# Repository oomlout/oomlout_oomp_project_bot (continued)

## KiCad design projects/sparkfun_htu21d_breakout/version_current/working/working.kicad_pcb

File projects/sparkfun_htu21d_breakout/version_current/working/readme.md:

# OOMP Project  
## HTU21D_Breakout  by sparkfun  
  
oomp key: oomp_projects_flat_sparkfun_htu21d_breakout  
(snippet of original readme)  
  
**NOTE:** *This product has been retired from our catalog. If you are looking for more up-to-date info, please check out some of these resources to see how other users are still hacking and improving on this product.*  
* *[SparkFun Forum](https://forum.sparkfun.com/)*  
* *[Comments Here on GitHub](https://github.com/sparkfun/HTU21D_Breakout/issues)*  
  
*We recommend looking at the [Si7021](https://www.sparkfun.com/products/13763), which is a drop-in replacement for the HTU21D. It uses the same address and methods to read the sensor.*  
  
SparkFun Humidity and Temperature Sensor Breakout - HTU21D  
===========================================================  

[*SparkFun Humidity and Temperature Sensor Breakout - HTU21D (SEN-12064)*](https://www.sparkfun.com/products/12064)  
  
This is a breadboard friendly breakout board for the Measurement Specialties high-precision, low-power digital humidity sensor.  
  
Repository Contents  
-------------------  
* **/Firmware** - Example code   
* **/Hardware** - Eagle design files (.brd, .sch)  
* **/Libraries** - Libraries for use with the <PRODUCT NAME>  
* **/Production** - Production panel files (.brd)  
  
Documentation  
--------------  
* **[Library](https://github.com/sparkfun/SparkFun_HTU21D_Breakout_Arduino_Library)** - Arduino library for the HTU21D.  
* **[Hookup Guide](https://learn.sparkfun.com/tutorials/htu21d-humidity-  
  full source readme at [readme_src.md](readme_src.md)  
  
source repo at: [https://github.com/sparkfun/HTU21D_Breakout](https://github.com/sparkfun/HTU21D_Breakout)  
## Board  

## Schematic  

[schematic pdf](working_schematic.pdf)  
## Images

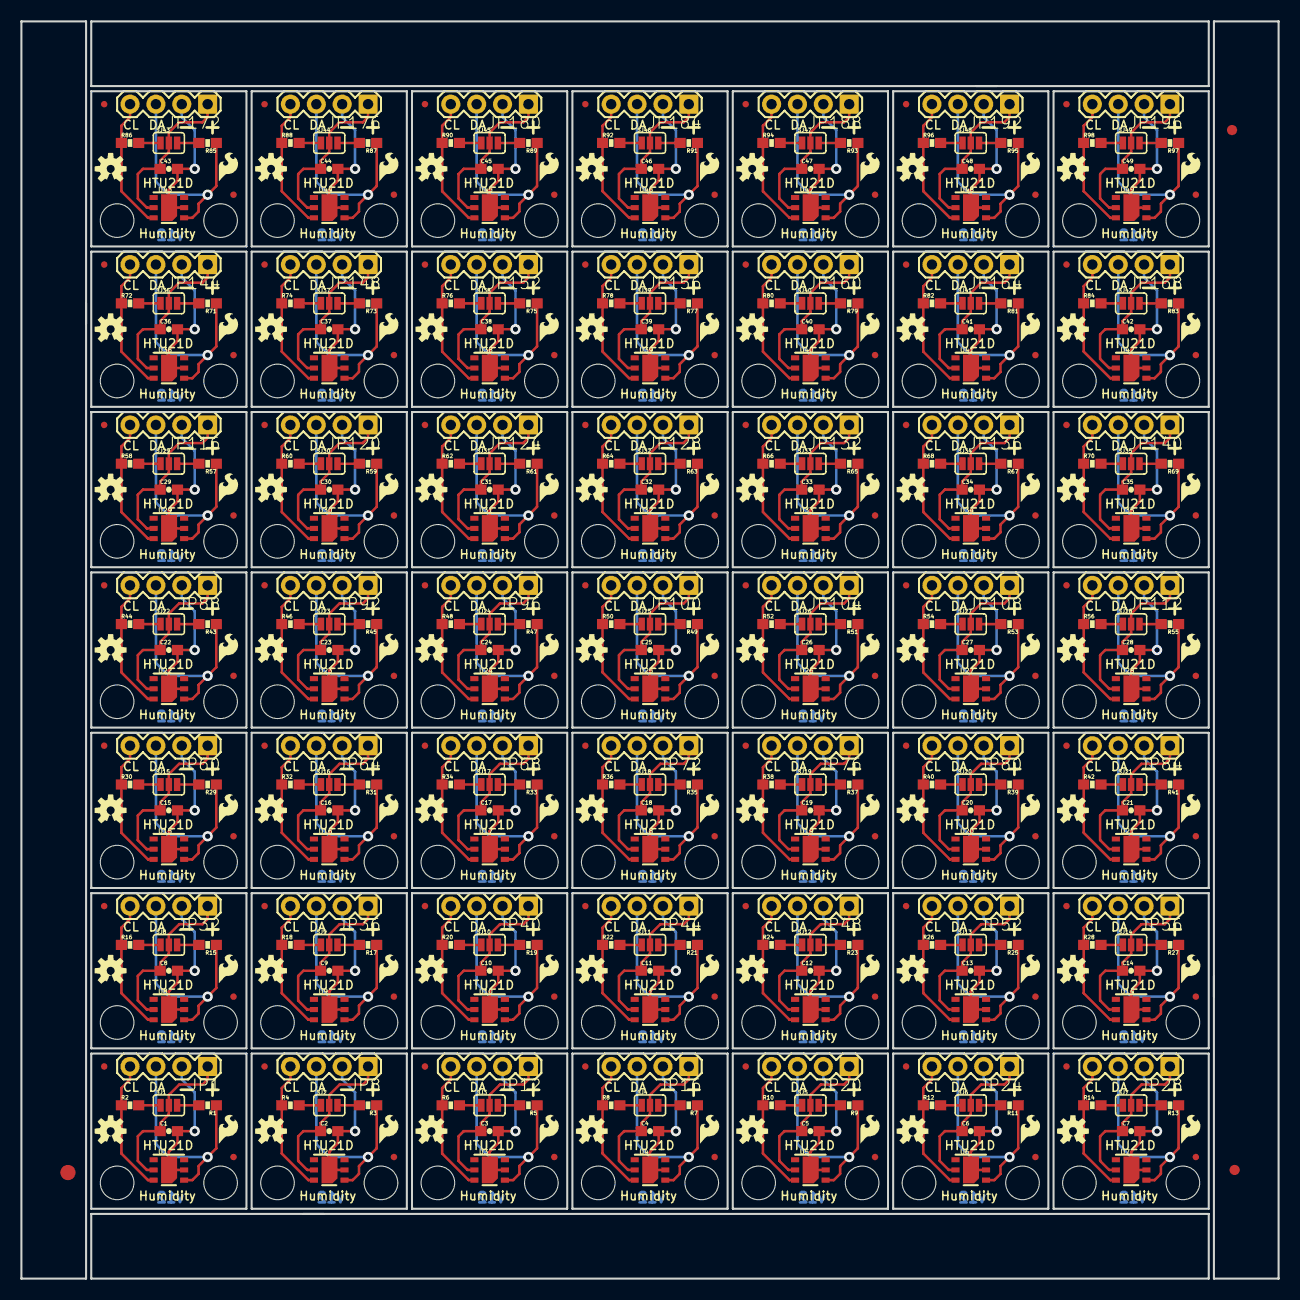
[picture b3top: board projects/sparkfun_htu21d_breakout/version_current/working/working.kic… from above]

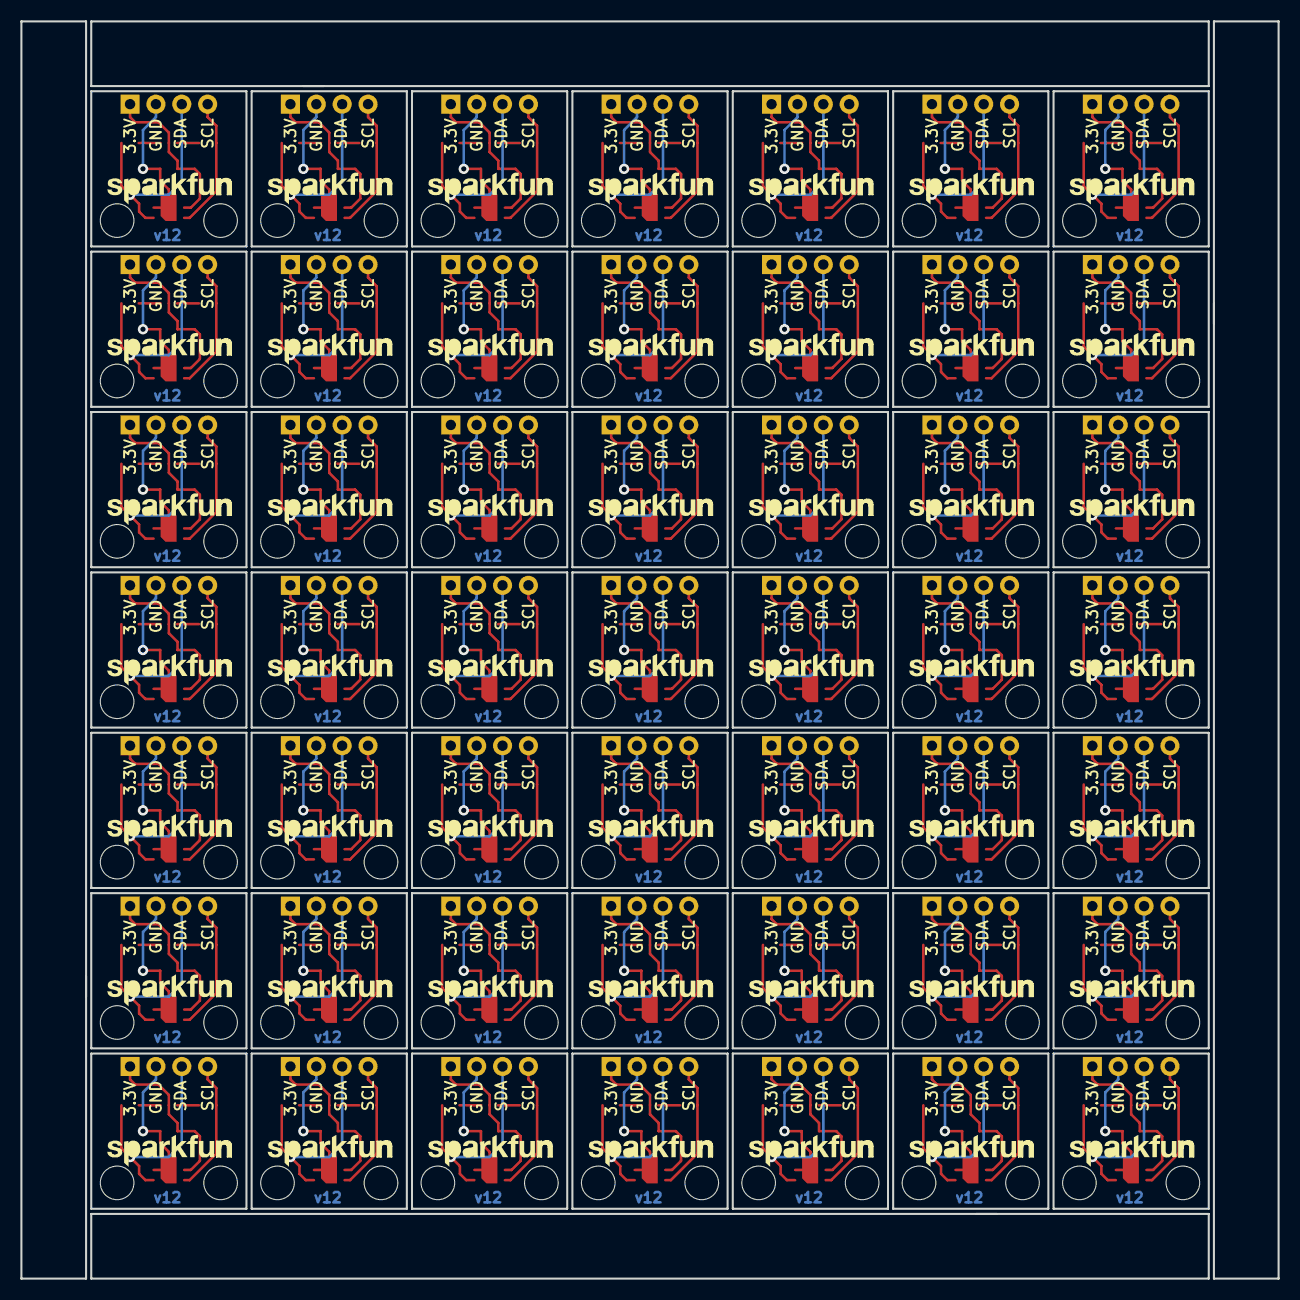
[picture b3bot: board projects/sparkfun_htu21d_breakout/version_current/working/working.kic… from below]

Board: 2 copper layers, 123.4 x 123.4 mm, 640 parts (49 on the bottom side), 294 nets.

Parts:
C1, C2, C3, C4, C5, C6, C7, C8, C9, C10, C11, C12, C13, C14, C15, C16, C17, C18, C19, C20, C21, C22, C23, C24, C25, C26, C27, C28, C29, C30, C31, C32, C33, C34, C35, C36, C37, C38, C39, C40, C41, C42, C43, C44, C45, C46, C47, C48, C49: 0.1uF; 0603-CAP
E$1: FIDUCIAL-1.5X3
E$4, E$5: FIDUCIAL-1X2
JP1, JP8, JP12, JP16, JP20, JP24, JP28, JP32, JP36, JP40, JP44, JP48, JP52, JP56, JP60, JP64, JP68, JP72, JP76, JP80, JP84, JP88, JP92, JP96, JP100, JP104, JP108, JP112, JP116, JP120, JP124, JP128, JP132, JP136, JP140, JP144, JP148, JP152, JP156, JP160, JP164, JP168, JP172, JP176, JP180, JP184, JP188, JP192, JP196: 1X04
JP2, JP5, JP9, JP13, JP17, JP21, JP25, JP29, JP33, JP37, JP41, JP45, JP49, JP53, JP57, JP61, JP65, JP69, JP73, JP77, JP81, JP85, JP89, JP93, JP97, JP101, JP105, JP109, JP113, JP117, JP121, JP125, JP129, JP133, JP137, JP141, JP145, JP149, JP153, JP157, JP161, JP165, JP169, JP173, JP177, JP181, JP185, JP189, JP193: LOGO-SFENW2; SFE-NEW-WEB
JP3, JP4, JP6, JP7, JP10, JP11, JP14, JP15, JP18, JP19, JP22, JP23, JP26, JP27, JP30, JP31, JP34, JP35, JP38, JP39, JP42, JP43, JP46, JP47, JP50, JP51, JP54, JP55, JP58, JP59, JP62, JP63, JP66, JP67, JP70, JP71, JP74, JP75, JP78, JP79, JP82, JP83, JP86, JP87, JP90, JP91, JP94, JP95, JP98, JP99, JP102, JP103, JP106, JP107, JP110, JP111, JP114, JP115, JP118, JP119, JP122, JP123, JP126, JP127, JP130, JP131, JP134, JP135, JP138, JP139, JP142, JP143, JP146, JP147, JP150, JP151, JP154, JP155, JP158, JP159, JP162, JP163, JP166, JP167, JP170, JP171, JP174, JP175, JP178, JP179, JP182, JP183, JP186, JP187, JP190, JP191, JP194, JP195: FIDUCIALUFIDUCIAL; MICRO-FIDUCIAL
LOGO1, LOGO3, LOGO5, LOGO7, LOGO9, LOGO11, LOGO13, LOGO15, LOGO17, LOGO19, LOGO21, LOGO23, LOGO25, LOGO27, LOGO29, LOGO31, LOGO33, LOGO35, LOGO37, LOGO39, LOGO41, LOGO43, LOGO45, LOGO47, LOGO49, LOGO51, LOGO53, LOGO55, LOGO57, LOGO59, LOGO61, LOGO63, LOGO65, LOGO67, LOGO69, LOGO71, LOGO73, LOGO75, LOGO77, LOGO79, LOGO81, LOGO83, LOGO85, LOGO87, LOGO89, LOGO91, LOGO93, LOGO95, LOGO97: LOGO-SFESK; SFE-LOGO-FLAME
LOGO2, LOGO4, LOGO6, LOGO8, LOGO10, LOGO12, LOGO14, LOGO16, LOGO18, LOGO20, LOGO22, LOGO24, LOGO26, LOGO28, LOGO30, LOGO32, LOGO34, LOGO36, LOGO38, LOGO40, LOGO42, LOGO44, LOGO46, LOGO48, LOGO50, LOGO52, LOGO54, LOGO56, LOGO58, LOGO60, LOGO62, LOGO64, LOGO66, LOGO68, LOGO70, LOGO72, LOGO74, LOGO76, LOGO78, LOGO80, LOGO82, LOGO84, LOGO86, LOGO88, LOGO90, LOGO92, LOGO94, LOGO96, LOGO98: OSHW-LOGOS; OSHW-LOGO-S
R1, R2, R3, R4, R5, R6, R7, R8, R9, R10, R11, R12, R13, R14, R15, R16, R17, R18, R19, R20, R21, R22, R23, R24, R25, R26, R27, R28, R29, R30, R31, R32, R33, R34, R35, R36, R37, R38, R39, R40, R41, R42, R43, R44, R45, R46, R47, R48, R49, R50, R51, R52, R53, R54, R55, R56, R57, R58, R59, R60, R61, R62, R63, R64, R65, R66, R67, R68, R69, R70, R71, R72, R73, R74, R75, R76, R77, R78, R79, R80, R81, R82, R83, R84, R85, R86, R87, R88, R89, R90, R91, R92, R93, R94, R95, R96, R97, R98: 4.7k; 0603-RES
SJ1, SJ2, SJ3, SJ4, SJ5, SJ6, SJ7, SJ8, SJ9, SJ10, SJ11, SJ12, SJ13, SJ14, SJ15, SJ16, SJ17, SJ18, SJ19, SJ20, SJ21, SJ22, SJ23, SJ24, SJ25, SJ26, SJ27, SJ28, SJ29, SJ30, SJ31, SJ32, SJ33, SJ34, SJ35, SJ36, SJ37, SJ38, SJ39, SJ40, SJ41, SJ42, SJ43, SJ44, SJ45, SJ46, SJ47, SJ48, SJ49: SJ_3_PASTE1&2&3
STANDOFF1, STANDOFF2, STANDOFF3, STANDOFF4, STANDOFF5, STANDOFF6, STANDOFF7, STANDOFF8, STANDOFF9, STANDOFF10, STANDOFF11, STANDOFF12, STANDOFF13, STANDOFF14, STANDOFF15, STANDOFF16, STANDOFF17, STANDOFF18, STANDOFF19, STANDOFF20, STANDOFF21, STANDOFF22, STANDOFF23, STANDOFF24, STANDOFF25, STANDOFF26, STANDOFF27, STANDOFF28, STANDOFF29, STANDOFF30, STANDOFF31, STANDOFF32, STANDOFF33, STANDOFF34, STANDOFF35, STANDOFF36, STANDOFF37, STANDOFF38, STANDOFF39, STANDOFF40, STANDOFF41, STANDOFF42, STANDOFF43, STANDOFF44, STANDOFF45, STANDOFF46, STANDOFF47, STANDOFF48, STANDOFF49, STANDOFF50, STANDOFF51, STANDOFF52, STANDOFF53, STANDOFF54, STANDOFF55, STANDOFF56, STANDOFF57, STANDOFF58, STANDOFF59, STANDOFF60, STANDOFF61, STANDOFF62, STANDOFF63, STANDOFF64, STANDOFF65, STANDOFF66, STANDOFF67, STANDOFF68, STANDOFF69, STANDOFF70, STANDOFF71, STANDOFF72, STANDOFF73, STANDOFF74, STANDOFF75, STANDOFF76, STANDOFF77, STANDOFF78, STANDOFF79, STANDOFF80, STANDOFF81, STANDOFF82, STANDOFF83, STANDOFF84, STANDOFF85, STANDOFF86, STANDOFF87, STANDOFF88, STANDOFF89, STANDOFF90, STANDOFF91, STANDOFF92, STANDOFF93, STANDOFF94, STANDOFF95, STANDOFF96, STANDOFF97, STANDOFF98: STAND-OFF
U1, U2, U3, U4, U5, U6, U7, U8, U9, U10, U11, U12, U13, U14, U15, U16, U17, U18, U19, U20, U21, U22, U23, U24, U25, U26, U27, U28, U29, U30, U31, U32, U33, U34, U35, U36, U37, U38, U39, U40, U41, U42, U43, U44, U45, U46, U47, U48, U49: HTU21D

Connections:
3.3V: C1.1, JP1.1, SJ1.2, U1.VDD
3.3V1: C2.1, JP8.1, SJ2.2, U2.VDD
3.3V2: C3.1, JP12.1, SJ3.2, U3.VDD
3.3V3: C4.1, JP16.1, SJ4.2, U4.VDD
3.3V4: C5.1, JP20.1, SJ5.2, U5.VDD
3.3V5: C6.1, JP24.1, SJ6.2, U6.VDD
3.3V6: C7.1, JP28.1, SJ7.2, U7.VDD
3.3V7: C8.1, JP32.1, SJ8.2, U8.VDD
3.3V8: C9.1, JP36.1, SJ9.2, U9.VDD
3.3V9: C10.1, JP40.1, SJ10.2, U10.VDD
3.3V10: C11.1, JP44.1, SJ11.2, U11.VDD
3.3V11: C12.1, JP48.1, SJ12.2, U12.VDD
3.3V12: C13.1, JP52.1, SJ13.2, U13.VDD
3.3V13: C14.1, JP56.1, SJ14.2, U14.VDD
3.3V14: C15.1, JP60.1, SJ15.2, U15.VDD
3.3V15: C16.1, JP64.1, SJ16.2, U16.VDD
3.3V16: C17.1, JP68.1, SJ17.2, U17.VDD
3.3V17: C18.1, JP72.1, SJ18.2, U18.VDD
3.3V18: C19.1, JP76.1, SJ19.2, U19.VDD
3.3V19: C20.1, JP80.1, SJ20.2, U20.VDD
3.3V20: C21.1, JP84.1, SJ21.2, U21.VDD
3.3V21: C22.1, JP88.1, SJ22.2, U22.VDD
3.3V22: C23.1, JP92.1, SJ23.2, U23.VDD
3.3V23: C24.1, JP96.1, SJ24.2, U24.VDD
3.3V24: C25.1, JP100.1, SJ25.2, U25.VDD
3.3V25: C26.1, JP104.1, SJ26.2, U26.VDD
3.3V26: C27.1, JP108.1, SJ27.2, U27.VDD
3.3V27: C28.1, JP112.1, SJ28.2, U28.VDD
3.3V28: C29.1, JP116.1, SJ29.2, U29.VDD
3.3V29: C30.1, JP120.1, SJ30.2, U30.VDD
3.3V30: C31.1, JP124.1, SJ31.2, U31.VDD
3.3V31: C32.1, JP128.1, SJ32.2, U32.VDD
3.3V32: C33.1, JP132.1, SJ33.2, U33.VDD
3.3V33: C34.1, JP136.1, SJ34.2, U34.VDD
3.3V34: C35.1, JP140.1, SJ35.2, U35.VDD
3.3V35: C36.1, JP144.1, SJ36.2, U36.VDD
3.3V36: C37.1, JP148.1, SJ37.2, U37.VDD
3.3V37: C38.1, JP152.1, SJ38.2, U38.VDD
3.3V38: C39.1, JP156.1, SJ39.2, U39.VDD
3.3V39: C40.1, JP160.1, SJ40.2, U40.VDD
3.3V40: C41.1, JP164.1, SJ41.2, U41.VDD
3.3V41: C42.1, JP168.1, SJ42.2, U42.VDD
3.3V42: C43.1, JP172.1, SJ43.2, U43.VDD
3.3V43: C44.1, JP176.1, SJ44.2, U44.VDD
3.3V44: C45.1, JP180.1, SJ45.2, U45.VDD
3.3V45: C46.1, JP184.1, SJ46.2, U46.VDD
3.3V46: C47.1, JP188.1, SJ47.2, U47.VDD
3.3V47: C48.1, JP192.1, SJ48.2, U48.VDD
3.3V48: C49.1, JP196.1, SJ49.2, U49.VDD
GND: C1.2, JP1.2, U1.7, U1.GND
GND1: C2.2, JP8.2, U2.7, U2.GND
GND2: C3.2, JP12.2, U3.7, U3.GND
GND3: C4.2, JP16.2, U4.7, U4.GND
GND4: C5.2, JP20.2, U5.7, U5.GND
GND5: C6.2, JP24.2, U6.7, U6.GND
GND6: C7.2, JP28.2, U7.7, U7.GND
GND7: C8.2, JP32.2, U8.7, U8.GND
GND8: C9.2, JP36.2, U9.7, U9.GND
GND9: C10.2, JP40.2, U10.7, U10.GND
GND10: C11.2, JP44.2, U11.7, U11.GND
GND11: C12.2, JP48.2, U12.7, U12.GND
GND12: C13.2, JP52.2, U13.7, U13.GND
GND13: C14.2, JP56.2, U14.7, U14.GND
GND14: C15.2, JP60.2, U15.7, U15.GND
GND15: C16.2, JP64.2, U16.7, U16.GND
GND16: C17.2, JP68.2, U17.7, U17.GND
GND17: C18.2, JP72.2, U18.7, U18.GND
GND18: C19.2, JP76.2, U19.7, U19.GND
GND19: C20.2, JP80.2, U20.7, U20.GND
GND20: C21.2, JP84.2, U21.7, U21.GND
GND21: C22.2, JP88.2, U22.7, U22.GND
GND22: C23.2, JP92.2, U23.7, U23.GND
GND23: C24.2, JP96.2, U24.7, U24.GND
GND24: C25.2, JP100.2, U25.7, U25.GND
GND25: C26.2, JP104.2, U26.7, U26.GND
GND26: C27.2, JP108.2, U27.7, U27.GND
GND27: C28.2, JP112.2, U28.7, U28.GND
GND28: C29.2, JP116.2, U29.7, U29.GND
GND29: C30.2, JP120.2, U30.7, U30.GND
GND30: C31.2, JP124.2, U31.7, U31.GND
GND31: C32.2, JP128.2, U32.7, U32.GND
GND32: C33.2, JP132.2, U33.7, U33.GND
GND33: C34.2, JP136.2, U34.7, U34.GND
GND34: C35.2, JP140.2, U35.7, U35.GND
GND35: C36.2, JP144.2, U36.7, U36.GND
GND36: C37.2, JP148.2, U37.7, U37.GND
GND37: C38.2, JP152.2, U38.7, U38.GND
GND38: C39.2, JP156.2, U39.7, U39.GND
GND39: C40.2, JP160.2, U40.7, U40.GND
GND40: C41.2, JP164.2, U41.7, U41.GND
GND41: C42.2, JP168.2, U42.7, U42.GND
GND42: C43.2, JP172.2, U43.7, U43.GND
GND43: C44.2, JP176.2, U44.7, U44.GND
GND44: C45.2, JP180.2, U45.7, U45.GND
GND45: C46.2, JP184.2, U46.7, U46.GND
GND46: C47.2, JP188.2, U47.7, U47.GND
GND47: C48.2, JP192.2, U48.7, U48.GND
GND48: C49.2, JP196.2, U49.7, U49.GND
unnamed: R1.2, SJ1.3
unnamed: R2.2, SJ1.1
unnamed: R3.2, SJ2.3
unnamed: R4.2, SJ2.1
unnamed: R5.2, SJ3.3
unnamed: R6.2, SJ3.1
unnamed: R7.2, SJ4.3
unnamed: R8.2, SJ4.1
unnamed: R9.2, SJ5.3
unnamed: R10.2, SJ5.1
unnamed: R11.2, SJ6.3
unnamed: R12.2, SJ6.1
unnamed: R13.2, SJ7.3
unnamed: R14.2, SJ7.1
unnamed: R15.2, SJ8.3
unnamed: R16.2, SJ8.1
unnamed: R17.2, SJ9.3
unnamed: R18.2, SJ9.1
unnamed: R19.2, SJ10.3
unnamed: R20.2, SJ10.1
unnamed: R21.2, SJ11.3
unnamed: R22.2, SJ11.1
unnamed: R23.2, SJ12.3
unnamed: R24.2, SJ12.1
unnamed: R25.2, SJ13.3
unnamed: R26.2, SJ13.1
unnamed: R27.2, SJ14.3
unnamed: R28.2, SJ14.1
unnamed: R29.2, SJ15.3
unnamed: R30.2, SJ15.1
unnamed: R31.2, SJ16.3
unnamed: R32.2, SJ16.1
unnamed: R33.2, SJ17.3
unnamed: R34.2, SJ17.1
unnamed: R35.2, SJ18.3
unnamed: R36.2, SJ18.1
unnamed: R37.2, SJ19.3
unnamed: R38.2, SJ19.1
unnamed: R39.2, SJ20.3
unnamed: R40.2, SJ20.1
unnamed: R41.2, SJ21.3
unnamed: R42.2, SJ21.1
unnamed: R43.2, SJ22.3
unnamed: R44.2, SJ22.1
unnamed: R45.2, SJ23.3
unnamed: R46.2, SJ23.1
unnamed: R47.2, SJ24.3
unnamed: R48.2, SJ24.1
unnamed: R49.2, SJ25.3
unnamed: R50.2, SJ25.1
unnamed: R51.2, SJ26.3
unnamed: R52.2, SJ26.1
unnamed: R53.2, SJ27.3
unnamed: R54.2, SJ27.1
unnamed: R55.2, SJ28.3
unnamed: R56.2, SJ28.1
unnamed: R57.2, SJ29.3
unnamed: R58.2, SJ29.1
unnamed: R59.2, SJ30.3
unnamed: R60.2, SJ30.1
unnamed: R61.2, SJ31.3
unnamed: R62.2, SJ31.1
unnamed: R63.2, SJ32.3
unnamed: R64.2, SJ32.1
unnamed: R65.2, SJ33.3
unnamed: R66.2, SJ33.1
unnamed: R67.2, SJ34.3
unnamed: R68.2, SJ34.1
unnamed: R69.2, SJ35.3
unnamed: R70.2, SJ35.1
unnamed: R71.2, SJ36.3
unnamed: R72.2, SJ36.1
unnamed: R73.2, SJ37.3
unnamed: R74.2, SJ37.1
unnamed: R75.2, SJ38.3
unnamed: R76.2, SJ38.1
unnamed: R77.2, SJ39.3
unnamed: R78.2, SJ39.1
unnamed: R79.2, SJ40.3
unnamed: R80.2, SJ40.1
unnamed: R81.2, SJ41.3
unnamed: R82.2, SJ41.1
unnamed: R83.2, SJ42.3
unnamed: R84.2, SJ42.1
unnamed: R85.2, SJ43.3
unnamed: R86.2, SJ43.1
unnamed: R87.2, SJ44.3
unnamed: R88.2, SJ44.1
unnamed: R89.2, SJ45.3
unnamed: R90.2, SJ45.1
unnamed: R91.2, SJ46.3
unnamed: R92.2, SJ46.1
unnamed: R93.2, SJ47.3
unnamed: R94.2, SJ47.1
unnamed: R95.2, SJ48.3
unnamed: R96.2, SJ48.1
unnamed: R97.2, SJ49.3
unnamed: R98.2, SJ49.1
SCL: JP1.4, R2.1, U1.SCK
SCL1: JP8.4, R4.1, U2.SCK
SCL2: JP12.4, R6.1, U3.SCK
SCL3: JP16.4, R8.1, U4.SCK
SCL4: JP20.4, R10.1, U5.SCK
SCL5: JP24.4, R12.1, U6.SCK
SCL6: JP28.4, R14.1, U7.SCK
SCL7: JP32.4, R16.1, U8.SCK
SCL8: JP36.4, R18.1, U9.SCK
SCL9: JP40.4, R20.1, U10.SCK
SCL10: JP44.4, R22.1, U11.SCK
SCL11: JP48.4, R24.1, U12.SCK
SCL12: JP52.4, R26.1, U13.SCK
SCL13: JP56.4, R28.1, U14.SCK
SCL14: JP60.4, R30.1, U15.SCK
SCL15: JP64.4, R32.1, U16.SCK
SCL16: JP68.4, R34.1, U17.SCK
SCL17: JP72.4, R36.1, U18.SCK
SCL18: JP76.4, R38.1, U19.SCK
SCL19: JP80.4, R40.1, U20.SCK
SCL20: JP84.4, R42.1, U21.SCK
SCL21: JP88.4, R44.1, U22.SCK
SCL22: JP92.4, R46.1, U23.SCK
SCL23: JP96.4, R48.1, U24.SCK
SCL24: JP100.4, R50.1, U25.SCK
SCL25: JP104.4, R52.1, U26.SCK
SCL26: JP108.4, R54.1, U27.SCK
SCL27: JP112.4, R56.1, U28.SCK
SCL28: JP116.4, R58.1, U29.SCK
SCL29: JP120.4, R60.1, U30.SCK
SCL30: JP124.4, R62.1, U31.SCK
SCL31: JP128.4, R64.1, U32.SCK
SCL32: JP132.4, R66.1, U33.SCK
SCL33: JP136.4, R68.1, U34.SCK
SCL34: JP140.4, R70.1, U35.SCK
SCL35: JP144.4, R72.1, U36.SCK
SCL36: JP148.4, R74.1, U37.SCK
SCL37: JP152.4, R76.1, U38.SCK
SCL38: JP156.4, R78.1, U39.SCK
SCL39: JP160.4, R80.1, U40.SCK
SCL40: JP164.4, R82.1, U41.SCK
SCL41: JP168.4, R84.1, U42.SCK
SCL42: JP172.4, R86.1, U43.SCK
SCL43: JP176.4, R88.1, U44.SCK
SCL44: JP180.4, R90.1, U45.SCK
SCL45: JP184.4, R92.1, U46.SCK
SCL46: JP188.4, R94.1, U47.SCK
SCL47: JP192.4, R96.1, U48.SCK
SCL48: JP196.4, R98.1, U49.SCK
SDA: JP1.3, R1.1, U1.DATA
SDA1: JP8.3, R3.1, U2.DATA
SDA2: JP12.3, R5.1, U3.DATA
SDA3: JP16.3, R7.1, U4.DATA
SDA4: JP20.3, R9.1, U5.DATA
SDA5: JP24.3, R11.1, U6.DATA
SDA6: JP28.3, R13.1, U7.DATA
SDA7: JP32.3, R15.1, U8.DATA
SDA8: JP36.3, R17.1, U9.DATA
SDA9: JP40.3, R19.1, U10.DATA
SDA10: JP44.3, R21.1, U11.DATA
SDA11: JP48.3, R23.1, U12.DATA
SDA12: JP52.3, R25.1, U13.DATA
SDA13: JP56.3, R27.1, U14.DATA
SDA14: JP60.3, R29.1, U15.DATA
SDA15: JP64.3, R31.1, U16.DATA
SDA16: JP68.3, R33.1, U17.DATA
SDA17: JP72.3, R35.1, U18.DATA
SDA18: JP76.3, R37.1, U19.DATA
SDA19: JP80.3, R39.1, U20.DATA
SDA20: JP84.3, R41.1, U21.DATA
SDA21: JP88.3, R43.1, U22.DATA
SDA22: JP92.3, R45.1, U23.DATA
SDA23: JP96.3, R47.1, U24.DATA
SDA24: JP100.3, R49.1, U25.DATA
SDA25: JP104.3, R51.1, U26.DATA
SDA26: JP108.3, R53.1, U27.DATA
SDA27: JP112.3, R55.1, U28.DATA
SDA28: JP116.3, R57.1, U29.DATA
SDA29: JP120.3, R59.1, U30.DATA
SDA30: JP124.3, R61.1, U31.DATA
SDA31: JP128.3, R63.1, U32.DATA
SDA32: JP132.3, R65.1, U33.DATA
SDA33: JP136.3, R67.1, U34.DATA
SDA34: JP140.3, R69.1, U35.DATA
SDA35: JP144.3, R71.1, U36.DATA
SDA36: JP148.3, R73.1, U37.DATA
SDA37: JP152.3, R75.1, U38.DATA
SDA38: JP156.3, R77.1, U39.DATA
SDA39: JP160.3, R79.1, U40.DATA
SDA40: JP164.3, R81.1, U41.DATA
SDA41: JP168.3, R83.1, U42.DATA
SDA42: JP172.3, R85.1, U43.DATA
SDA43: JP176.3, R87.1, U44.DATA
SDA44: JP180.3, R89.1, U45.DATA
SDA45: JP184.3, R91.1, U46.DATA
SDA46: JP188.3, R93.1, U47.DATA
SDA47: JP192.3, R95.1, U48.DATA
SDA48: JP196.3, R97.1, U49.DATA

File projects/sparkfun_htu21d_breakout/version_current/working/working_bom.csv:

Row,Description,Part,References,Value,Footprint,Quantity Per PCB,Status,Datasheet
1,,CAP0603-CAP,C1,0.1uF,0603-CAP,1, ,
2,,FRAME-LETTER,FRAME2,FRAME-LETTER,CREATIVE_COMMONS,1, ,
3,,SparkFun-Aesthetics_LOGO-SFENW2,JP2,LOGO-SFENW2,SFE-NEW-WEB,1, ,
4,,M04PTH,JP1,M04PTH,1X04,1, ,
5,,LOGO-SFESK,LOGO1,LOGO-SFESK,SFE-LOGO-FLAME,1, ,
6,,OSHW-LOGOS,LOGO2,OSHW-LOGOS,OSHW-LOGO-S,1, ,
7,,RESISTOR0603-RES,R1 R2,4.7k,0603-RES,2, ,
8,,STAND-OFF,STANDOFF1 STANDOFF2,STAND-OFF,STAND-OFF,2, ,
9,,HTU21DSMD,U1,HTU21DSMD,HTU21D,1, ,





Project info:
Schematic:,working
Variant:,default
Revision:,
Date:,2023-08-06_12-56-03
KiCad Version:,7.0.6-7.0.6~ubuntu22.04.1
Statistics:
Component Groups:,9
Component Count:,11 (0 SMD/ 0 THT)
Fitted Components:,11 (0 SMD/ 0 THT)
Number of PCBs:,1
Total Components:,11

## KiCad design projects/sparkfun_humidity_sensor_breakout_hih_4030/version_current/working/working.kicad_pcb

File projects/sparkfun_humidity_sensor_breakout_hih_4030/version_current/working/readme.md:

# OOMP Project  
## Humidity_Sensor_Breakout-HIH-4030  by sparkfun  
  
oomp key: oomp_projects_flat_sparkfun_humidity_sensor_breakout_hih_4030  
(snippet of original readme)  
  
SparkFun Humidity Sensor Breakout - HIH-4030  
========================================  

[*SparkFun Humidity Sensor Breakout - HIH-4030 (SEN-09569)*](https://www.sparkfun.com/products/9569)  
  
This is a breakout board for Honeywell’s HIH-4030 humidity sensor.   
The HIH-4030 measures relative humidity (%RH) and delivers it as an analog output voltage.   
  
Repository Contents  
-------------------  
  
* **/Hardware** - Eagle design files (.brd, .sch)  
* **/Production** - Production panel files (.brd)  
  
Documentation  
--------------  
* **[SparkFun Fritzing repo](https://github.com/sparkfun/Fritzing_Parts)** - Fritzing diagrams for SparkFun products.  
* **[SparkFun 3D Model repo](https://github.com/sparkfun/3D_Models)** - 3D models of SparkFun products.   

License Information  
-------------------  
This product is _**open source**_!   
  
The **hardware** is released under [Creative Commons ShareAlike 4.0 International](https://creativecommons.org/licenses/by-sa/4.0/).  
  
Please use, reuse, and modify these files as you see fit. Please maintain attribution to SparkFun Electronics and release anything derivative under the same license.  
  
Distributed as-is; no warranty is given.  
  
- Your friends at SparkFun.  

  full source readme at [readme_src.md](readme_src.md)  
  
source repo at: [https://github.com/sparkfun/Humidity_Sensor_Breakout-HIH-4030](https://github.com/sparkfun/Humidity_Sensor_Breakout-HIH-4030)  
## Board  

## Schematic  

[schematic pdf](working_schematic.pdf)  
## Images

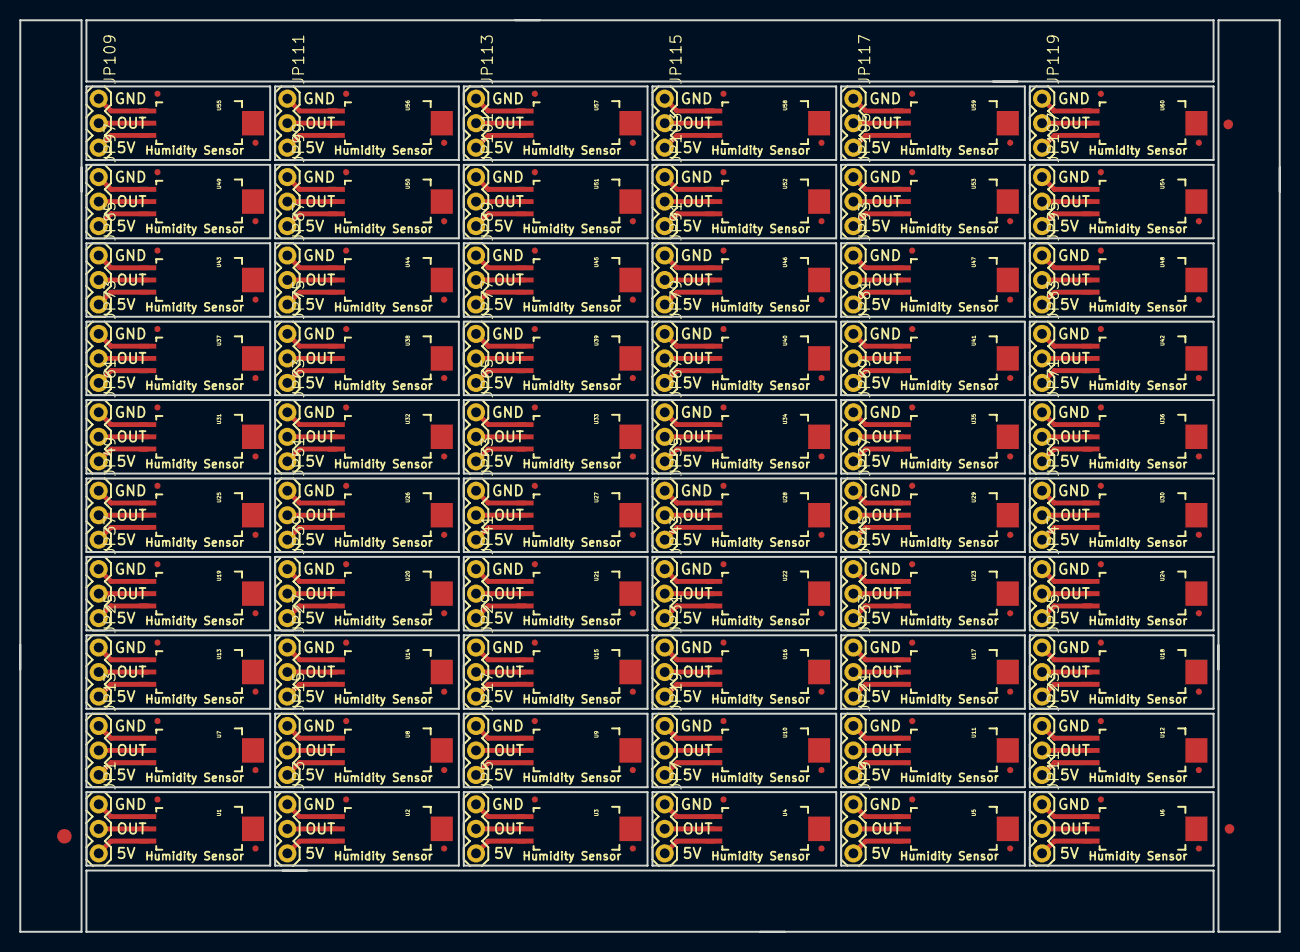
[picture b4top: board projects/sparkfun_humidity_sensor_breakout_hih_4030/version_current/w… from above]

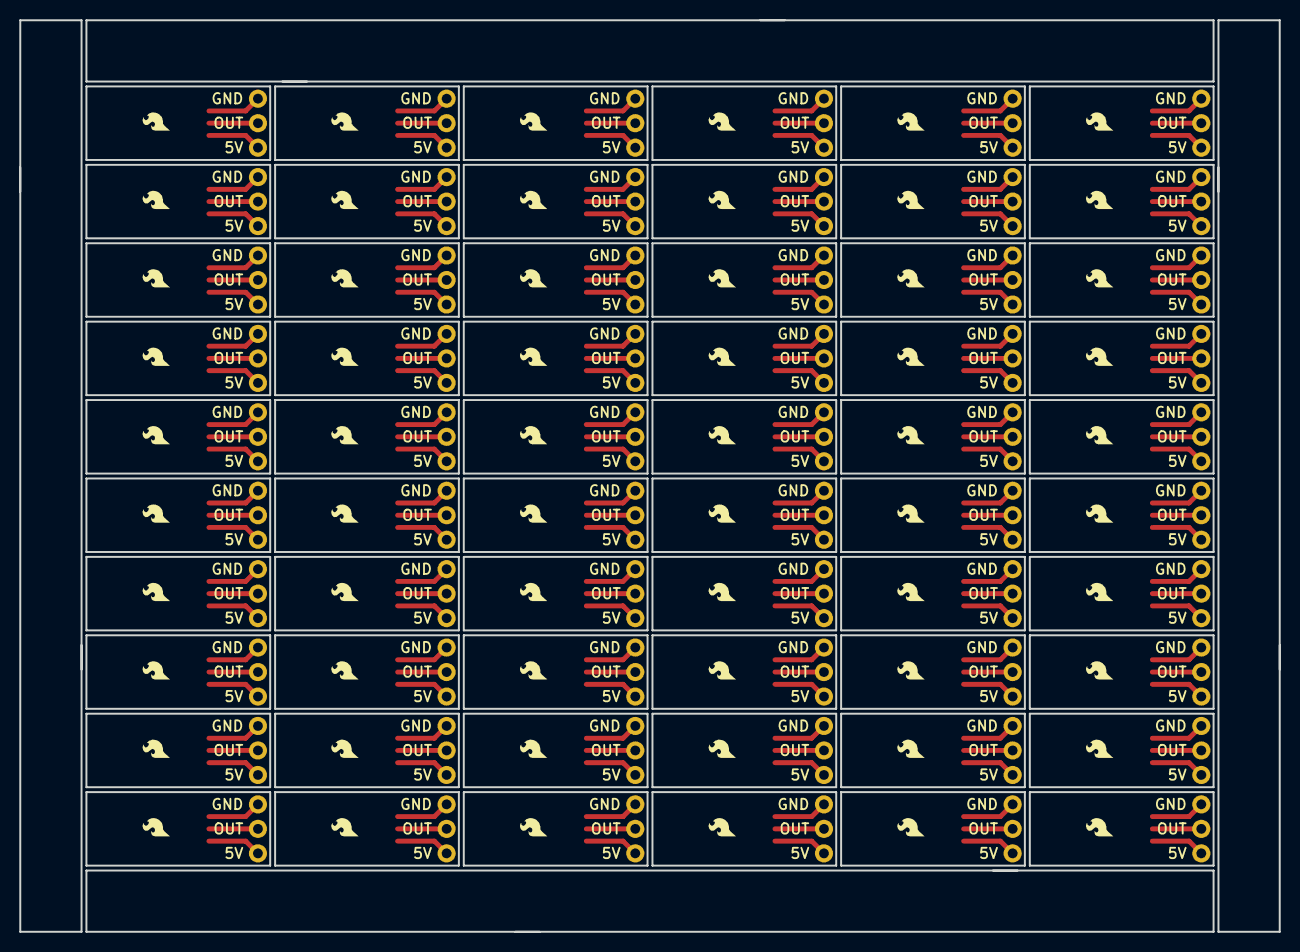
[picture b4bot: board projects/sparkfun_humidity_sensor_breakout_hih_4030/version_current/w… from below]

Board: 2 copper layers, 130.6 x 94.5 mm, 303 parts (60 on the bottom side), 180 nets.

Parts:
E$1: FIDUCIAL-1.5X3
E$5, E$7: FIDUCIAL-1X2
FID1, FID2, FID3, FID4, FID5, FID6, FID7, FID8, FID9, FID10, FID11, FID12, FID13, FID14, FID15, FID16, FID17, FID18, FID19, FID20, FID21, FID22, FID23, FID24, FID25, FID26, FID27, FID28, FID29, FID30, FID31, FID32, FID33, FID34, FID35, FID36, FID37, FID38, FID39, FID40, FID41, FID42, FID43, FID44, FID45, FID46, FID47, FID48, FID49, FID50, FID51, FID52, FID53, FID54, FID55, FID56, FID57, FID58, FID59, FID60, FID61, FID62, FID63, FID64, FID65, FID66, FID67, FID68, FID69, FID70, FID71, FID72, FID73, FID74, FID75, FID76, FID77, FID78, FID79, FID80, FID81, FID82, FID83, FID84, FID85, FID86, FID87, FID88, FID89, FID90, FID91, FID92, FID93, FID94, FID95, FID96, FID97, FID98, FID99, FID100, FID101, FID102, FID103, FID104, FID105, FID106, FID107, FID108, FID109, FID110, FID111, FID112, FID113, FID114, FID115, FID116, FID117, FID118, FID119, FID120: FIDUCIALUFIDUCIAL; MICRO-FIDUCIAL
JP1, JP3, JP5, JP7, JP9, JP11, JP13, JP15, JP17, JP19, JP21, JP23, JP25, JP27, JP29, JP31, JP33, JP35, JP37, JP39, JP41, JP43, JP45, JP47, JP49, JP51, JP53, JP55, JP57, JP59, JP61, JP63, JP65, JP67, JP69, JP71, JP73, JP75, JP77, JP79, JP81, JP83, JP85, JP87, JP89, JP91, JP93, JP95, JP97, JP99, JP101, JP103, JP105, JP107, JP109, JP111, JP113, JP115, JP117, JP119: 1X03
JP2, JP4, JP6, JP8, JP10, JP12, JP14, JP16, JP18, JP20, JP22, JP24, JP26, JP28, JP30, JP32, JP34, JP36, JP38, JP40, JP42, JP44, JP46, JP48, JP50, JP52, JP54, JP56, JP58, JP60, JP62, JP64, JP66, JP68, JP70, JP72, JP74, JP76, JP78, JP80, JP82, JP84, JP86, JP88, JP90, JP92, JP94, JP96, JP98, JP100, JP102, JP104, JP106, JP108, JP110, JP112, JP114, JP116, JP118, JP120: LOGO-SFESK; SFE-LOGO-FLAME
U1, U2, U3, U4, U5, U6, U7, U8, U9, U10, U11, U12, U13, U14, U15, U16, U17, U18, U19, U20, U21, U22, U23, U24, U25, U26, U27, U28, U29, U30, U31, U32, U33, U34, U35, U36, U37, U38, U39, U40, U41, U42, U43, U44, U45, U46, U47, U48, U49, U50, U51, U52, U53, U54, U55, U56, U57, U58, U59, U60: HIH-4030SMD; HIH-4030

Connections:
GND: JP1.1, U1.1
GND1: JP3.1, U2.1
GND2: JP5.1, U3.1
GND3: JP7.1, U4.1
GND4: JP9.1, U5.1
GND5: JP11.1, U6.1
GND6: JP13.1, U7.1
GND7: JP15.1, U8.1
GND8: JP17.1, U9.1
GND9: JP19.1, U10.1
GND10: JP21.1, U11.1
GND11: JP23.1, U12.1
GND12: JP25.1, U13.1
GND13: JP27.1, U14.1
GND14: JP29.1, U15.1
GND15: JP31.1, U16.1
GND16: JP33.1, U17.1
GND17: JP35.1, U18.1
GND18: JP37.1, U19.1
GND19: JP39.1, U20.1
GND20: JP41.1, U21.1
GND21: JP43.1, U22.1
GND22: JP45.1, U23.1
GND23: JP47.1, U24.1
GND24: JP49.1, U25.1
GND25: JP51.1, U26.1
GND26: JP53.1, U27.1
GND27: JP55.1, U28.1
GND28: JP57.1, U29.1
GND29: JP59.1, U30.1
GND30: JP61.1, U31.1
GND31: JP63.1, U32.1
GND32: JP65.1, U33.1
GND33: JP67.1, U34.1
GND34: JP69.1, U35.1
GND35: JP71.1, U36.1
GND36: JP73.1, U37.1
GND37: JP75.1, U38.1
GND38: JP77.1, U39.1
GND39: JP79.1, U40.1
GND40: JP81.1, U41.1
GND41: JP83.1, U42.1
GND42: JP85.1, U43.1
GND43: JP87.1, U44.1
GND44: JP89.1, U45.1
GND45: JP91.1, U46.1
GND46: JP93.1, U47.1
GND47: JP95.1, U48.1
GND48: JP97.1, U49.1
GND49: JP99.1, U50.1
GND50: JP101.1, U51.1
GND51: JP103.1, U52.1
GND52: JP105.1, U53.1
GND53: JP107.1, U54.1
GND54: JP109.1, U55.1
GND55: JP111.1, U56.1
GND56: JP113.1, U57.1
GND57: JP115.1, U58.1
GND58: JP117.1, U59.1
GND59: JP119.1, U60.1
OUT: JP1.2, U1.2
OUT1: JP3.2, U2.2
OUT2: JP5.2, U3.2
OUT3: JP7.2, U4.2
OUT4: JP9.2, U5.2
OUT5: JP11.2, U6.2
OUT6: JP13.2, U7.2
OUT7: JP15.2, U8.2
OUT8: JP17.2, U9.2
OUT9: JP19.2, U10.2
OUT10: JP21.2, U11.2
OUT11: JP23.2, U12.2
OUT12: JP25.2, U13.2
OUT13: JP27.2, U14.2
OUT14: JP29.2, U15.2
OUT15: JP31.2, U16.2
OUT16: JP33.2, U17.2
OUT17: JP35.2, U18.2
OUT18: JP37.2, U19.2
OUT19: JP39.2, U20.2
OUT20: JP41.2, U21.2
OUT21: JP43.2, U22.2
OUT22: JP45.2, U23.2
OUT23: JP47.2, U24.2
OUT24: JP49.2, U25.2
OUT25: JP51.2, U26.2
OUT26: JP53.2, U27.2
OUT27: JP55.2, U28.2
OUT28: JP57.2, U29.2
OUT29: JP59.2, U30.2
OUT30: JP61.2, U31.2
OUT31: JP63.2, U32.2
OUT32: JP65.2, U33.2
OUT33: JP67.2, U34.2
OUT34: JP69.2, U35.2
OUT35: JP71.2, U36.2
OUT36: JP73.2, U37.2
OUT37: JP75.2, U38.2
OUT38: JP77.2, U39.2
OUT39: JP79.2, U40.2
OUT40: JP81.2, U41.2
OUT41: JP83.2, U42.2
OUT42: JP85.2, U43.2
OUT43: JP87.2, U44.2
OUT44: JP89.2, U45.2
OUT45: JP91.2, U46.2
OUT46: JP93.2, U47.2
OUT47: JP95.2, U48.2
OUT48: JP97.2, U49.2
OUT49: JP99.2, U50.2
OUT50: JP101.2, U51.2
OUT51: JP103.2, U52.2
OUT52: JP105.2, U53.2
OUT53: JP107.2, U54.2
OUT54: JP109.2, U55.2
OUT55: JP111.2, U56.2
OUT56: JP113.2, U57.2
OUT57: JP115.2, U58.2
OUT58: JP117.2, U59.2
OUT59: JP119.2, U60.2
VCC: JP1.3, U1.3
VCC1: JP3.3, U2.3
VCC2: JP5.3, U3.3
VCC3: JP7.3, U4.3
VCC4: JP9.3, U5.3
VCC5: JP11.3, U6.3
VCC6: JP13.3, U7.3
VCC7: JP15.3, U8.3
VCC8: JP17.3, U9.3
VCC9: JP19.3, U10.3
VCC10: JP21.3, U11.3
VCC11: JP23.3, U12.3
VCC12: JP25.3, U13.3
VCC13: JP27.3, U14.3
VCC14: JP29.3, U15.3
VCC15: JP31.3, U16.3
VCC16: JP33.3, U17.3
VCC17: JP35.3, U18.3
VCC18: JP37.3, U19.3
VCC19: JP39.3, U20.3
VCC20: JP41.3, U21.3
VCC21: JP43.3, U22.3
VCC22: JP45.3, U23.3
VCC23: JP47.3, U24.3
VCC24: JP49.3, U25.3
VCC25: JP51.3, U26.3
VCC26: JP53.3, U27.3
VCC27: JP55.3, U28.3
VCC28: JP57.3, U29.3
VCC29: JP59.3, U30.3
VCC30: JP61.3, U31.3
VCC31: JP63.3, U32.3
VCC32: JP65.3, U33.3
VCC33: JP67.3, U34.3
VCC34: JP69.3, U35.3
VCC35: JP71.3, U36.3
VCC36: JP73.3, U37.3
VCC37: JP75.3, U38.3
VCC38: JP77.3, U39.3
VCC39: JP79.3, U40.3
VCC40: JP81.3, U41.3
VCC41: JP83.3, U42.3
VCC42: JP85.3, U43.3
VCC43: JP87.3, U44.3
VCC44: JP89.3, U45.3
VCC45: JP91.3, U46.3
VCC46: JP93.3, U47.3
VCC47: JP95.3, U48.3
VCC48: JP97.3, U49.3
VCC49: JP99.3, U50.3
VCC50: JP101.3, U51.3
VCC51: JP103.3, U52.3
VCC52: JP105.3, U53.3
VCC53: JP107.3, U54.3
VCC54: JP109.3, U55.3
VCC55: JP111.3, U56.3
VCC56: JP113.3, U57.3
VCC57: JP115.3, U58.3
VCC58: JP117.3, U59.3
VCC59: JP119.3, U60.3

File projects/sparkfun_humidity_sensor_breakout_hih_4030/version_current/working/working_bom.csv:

"Id";"Designator";"Footprint";"Quantity";"Designation";"Supplier and ref";
1;"U30,U58,U54,U33,U25,U15,U8,U41,U16,U42,U17,U51,U24,U7,U36,U52,U14,U35,U11,U12,U19,U21,U9,U50,U43,U60,U45,U53,U13,U56,U6,U48,U57,U2,U31,U22,U59,U38,U44,U28,U3,U29,U23,U49,U18,U26,U55,U20,U32,U46,U39,U47,U27,U4,U40,U5,U10,U37,U1,U34";"HIH-4030";60;"HIH-4030SMD";;;
2;"FID116,FID34,FID82,FID114,FID102,FID6,FID104,FID75,FID61,FID42,FID32,FID100,FID76,FID60,FID16,FID5,FID55,FID72,FID87,FID29,FID2,FID46,FID37,FID105,FID111,FID98,FID59,FID47,FID3,FID18,FID36,FID115,FID107,FID96,FID12,FID118,FID88,FID80,FID35,FID99,FID26,FID7,FID101,FID30,FID1,FID109,FID38,FID103,FID33,FID117,FID69,FID48,FID57,FID92,FID64,FID106,FID77,FID15,FID54,FID79,FID70,FID65,FID112,FID44,FID73,FID11,FID58,FID63,FID17,FID86,FID52,FID24,FID39,FID74,FID93,FID23,FID110,FID51,FID68,FID8,FID56,FID120,FID49,FID71,FID94,FID62,FID28,FID83,FID27,FID13,FID25,FID40,FID89,FID4,FID31,FID67,FID78,FID50,FID97,FID10,FID90,FID113,FID53,FID66,FID20,FID119,FID45,FID19,FID81,FID95,FID91,FID84,FID85,FID108,FID41,FID14,FID21,FID43,FID9,FID22";"MICRO-FIDUCIAL";120;"FIDUCIALUFIDUCIAL";;;
3;"JP55,JP1,JP45,JP63,JP39,JP21,JP115,JP17,JP19,JP43,JP89,JP111,JP51,JP81,JP71,JP95,JP5,JP117,JP33,JP9,JP87,JP27,JP77,JP113,JP107,JP25,JP31,JP59,JP61,JP97,JP3,JP11,JP85,JP119,JP105,JP29,JP49,JP67,JP37,JP93,JP57,JP101,JP13,JP65,JP83,JP79,JP35,JP103,JP15,JP41,JP109,JP47,JP23,JP99,JP69,JP7,JP73,JP75,JP91,JP53";"1X03";60;"";;;
4;"E$7,E$5";"FIDUCIAL-1X2";2;"";;;
5;"E$1";"FIDUCIAL-1.5X3";1;"";;;
6;"JP36,JP24,JP74,JP108,JP80,JP86,JP14,JP6,JP26,JP94,JP10,JP38,JP44,JP104,JP16,JP106,JP40,JP82,JP58,JP72,JP52,JP118,JP4,JP66,JP42,JP22,JP28,JP114,JP48,JP78,JP56,JP32,JP18,JP112,JP92,JP110,JP34,JP116,JP46,JP100,JP54,JP62,JP60,JP2,JP70,JP12,JP120,JP64,JP96,JP68,JP76,JP88,JP30,JP20,JP90,JP102,JP50,JP8,JP84,JP98";"SFE-LOGO-FLAME";60;"LOGO-SFESK";;;
